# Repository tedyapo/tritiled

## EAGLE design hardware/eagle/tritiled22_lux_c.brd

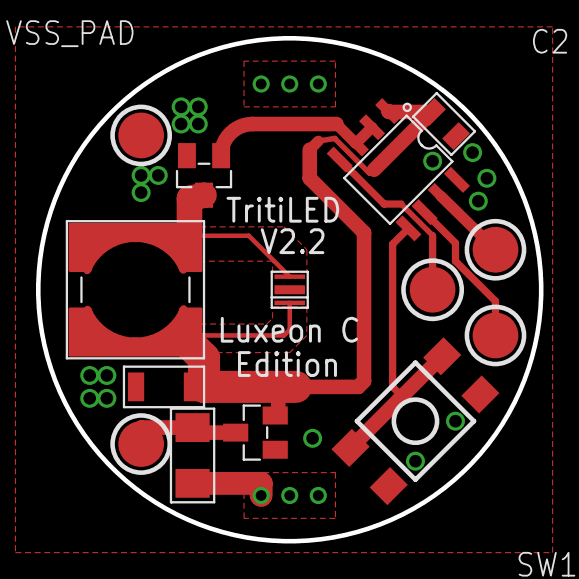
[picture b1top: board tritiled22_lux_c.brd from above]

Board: 2 copper layers, 27.9 x 27.9 mm, 15 parts (1 on the bottom side), 10 nets.

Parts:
B1: BAT-HLD-001_CR2032; CR2032_BAT-HLD_001
C1: 10u; 1206
C2: 100n; 0805
D1: Luxeon C; LUXEON_C
ICSPCLK_PAD: ICSP_PAD
ICSPDAT_PAD: ICSP_PAD
L1: 1m; SRR6028_INDUCTOR
MCLR_PAD: ICSP_PAD
Q1: ZXMN3B01FTA; SOT-23
Q2: DMG2305UX; SOT-23
R1: 100; R1206
SW1: SMD_SWITCH
U1: PIC12LF1571; SOIC8
VDD_PAD: ICSP_PAD
VSS_PAD: ICSP_PAD

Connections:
+3.3V: C1.P$1, C2.P$1, D1.C, L1.P$1, Q2.2, U1.1
GND: B1.GND, C1.P$2, C2.P$2, Q1.2, Q2.1, SW1.P$3, SW1.P$4, U1.8, VSS_PAD.P$2
unnamed: MCLR_PAD.P$2, U1.4
unnamed: ICSPDAT_PAD.P$2, U1.7
unnamed: ICSPCLK_PAD.P$2, U1.6
unnamed: D1.A, L1.P$2, Q1.3
unnamed: SW1.P$1, SW1.P$2, U1.5
unnamed: Q1.1, U1.2, U1.3
VBATT: B1.+V1, B1.+V2, R1.P$1
VSAFE: Q2.3, R1.P$2, VDD_PAD.P$2

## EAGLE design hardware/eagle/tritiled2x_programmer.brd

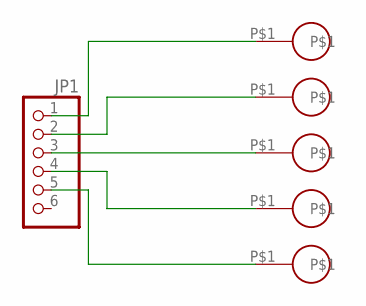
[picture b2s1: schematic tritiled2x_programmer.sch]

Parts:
JP1: PINHD-1X6; 1X06
U$1, U$2, U$3, U$4, U$5: SPRING_PIN

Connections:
ICSPCLK: JP1.5, U$5.P$1
ICSPDAT: JP1.4, U$4.P$1
VDD: JP1.2, U$2.P$1
VPP: JP1.1, U$1.P$1
VSS: JP1.3, U$3.P$1

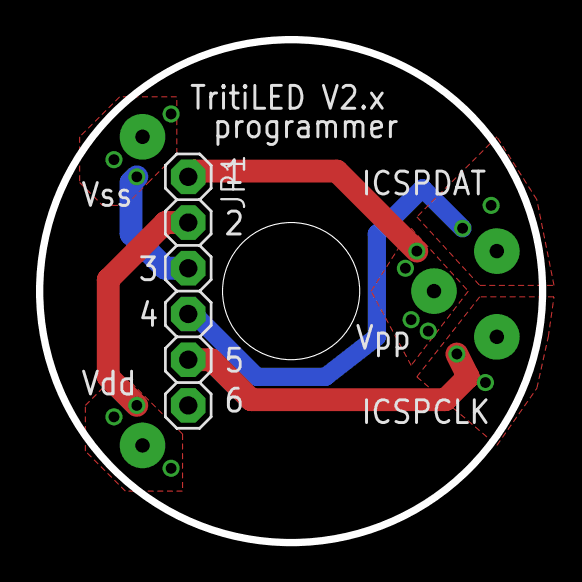
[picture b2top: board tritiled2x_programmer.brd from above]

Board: 2 copper layers, 27.9 x 27.9 mm, 6 parts (0 on the bottom side), 5 nets.
